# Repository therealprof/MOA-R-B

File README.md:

# The MOA(R)B (or mother of all Rust boards)

The MOA(R)B is a proof of concept proto board which breaks out 4 MCUs from
different vendors which are readily supported by the Rust programming language
and adds a DAP42 USB debugger/programmer with virtual serial port as well as
the requisite USB port and voltage regulator for good measure.

## What exactly is it?

The MOA(R)B was developed to demonstrate how easy it is to design and manufacture Rust-able microcontroller designs. The original plan was to give a talk about this at Oxidize 2019 but that didn't happen. The board is still the first iteration (with a minor fix applied) and I don't expect to further update it. However feel free to take the full or parts of the design and do whatever you want with it.

The following MCUs are supported (but compatible footprints might be used as well):
* ST STM32F042F6Px
* NXP LPC824M201JDH20
* EByte E73-2G4M04S-52832 (a BLE capable module based on the Nordic NRF52832)
* Atmel/Microchip ATSAMD21E15A

In addition another STM32F042F6P6 can be populated as DAPlink compatible debugger/programmer with virtual serial port.

## How to build the boards?

I've included an interactive HTML BOM and population guide [here](bom/ibom.html).

**NOTE**: If you happen to have one of the 10 first run boards you will need to add a shame wire from pad 15 of the DAPlink MCU to ground -- if you want to populate and use the onboard debugger, that is. If you work with the published version 1.1 there're no known errata.

### Functional blocks

* Voltage regulator: If you want to automatic 3.3V generation and distribution, this is a must have. You should also populate J5 then, which connect the 3.3V to the MCUs when the link is shorted
* USB input: You obviously want to have this if you want to power the board from USB and/or use the onboard debugger (in this case you might also want to consider populating the TVS protection diode)
* Debugger: Obviously you only need this if you'd like to have the onboard debugger. The purpose of the SWD connector and J6 is to connect the SWD lines to the onboard debugger but also for standalone conversion if you have an external debugger or you'd like to use this debugger for external devices -- so many choices!
* LEDs: Who doesn't like blinkies? The 4 MCU leds are indicators for powered MCUs the other ones can either be used for the debugger or alternatively for any of the MCUs.
* The MCUs are completely optional and fully broken out to commonly used 2.54mm spacing so populate and use whichever you want to use. The capacitors next to the MCUs should be populated for decoupling. Most likely you also want to have the matching pins on the backside; those can either be long enough straight headers or SMD headers.

## Can I reuse the hardware for my own ideas?

Absolutely, everything is licensed under the BSD license so please go ahead and use it however you'd like.

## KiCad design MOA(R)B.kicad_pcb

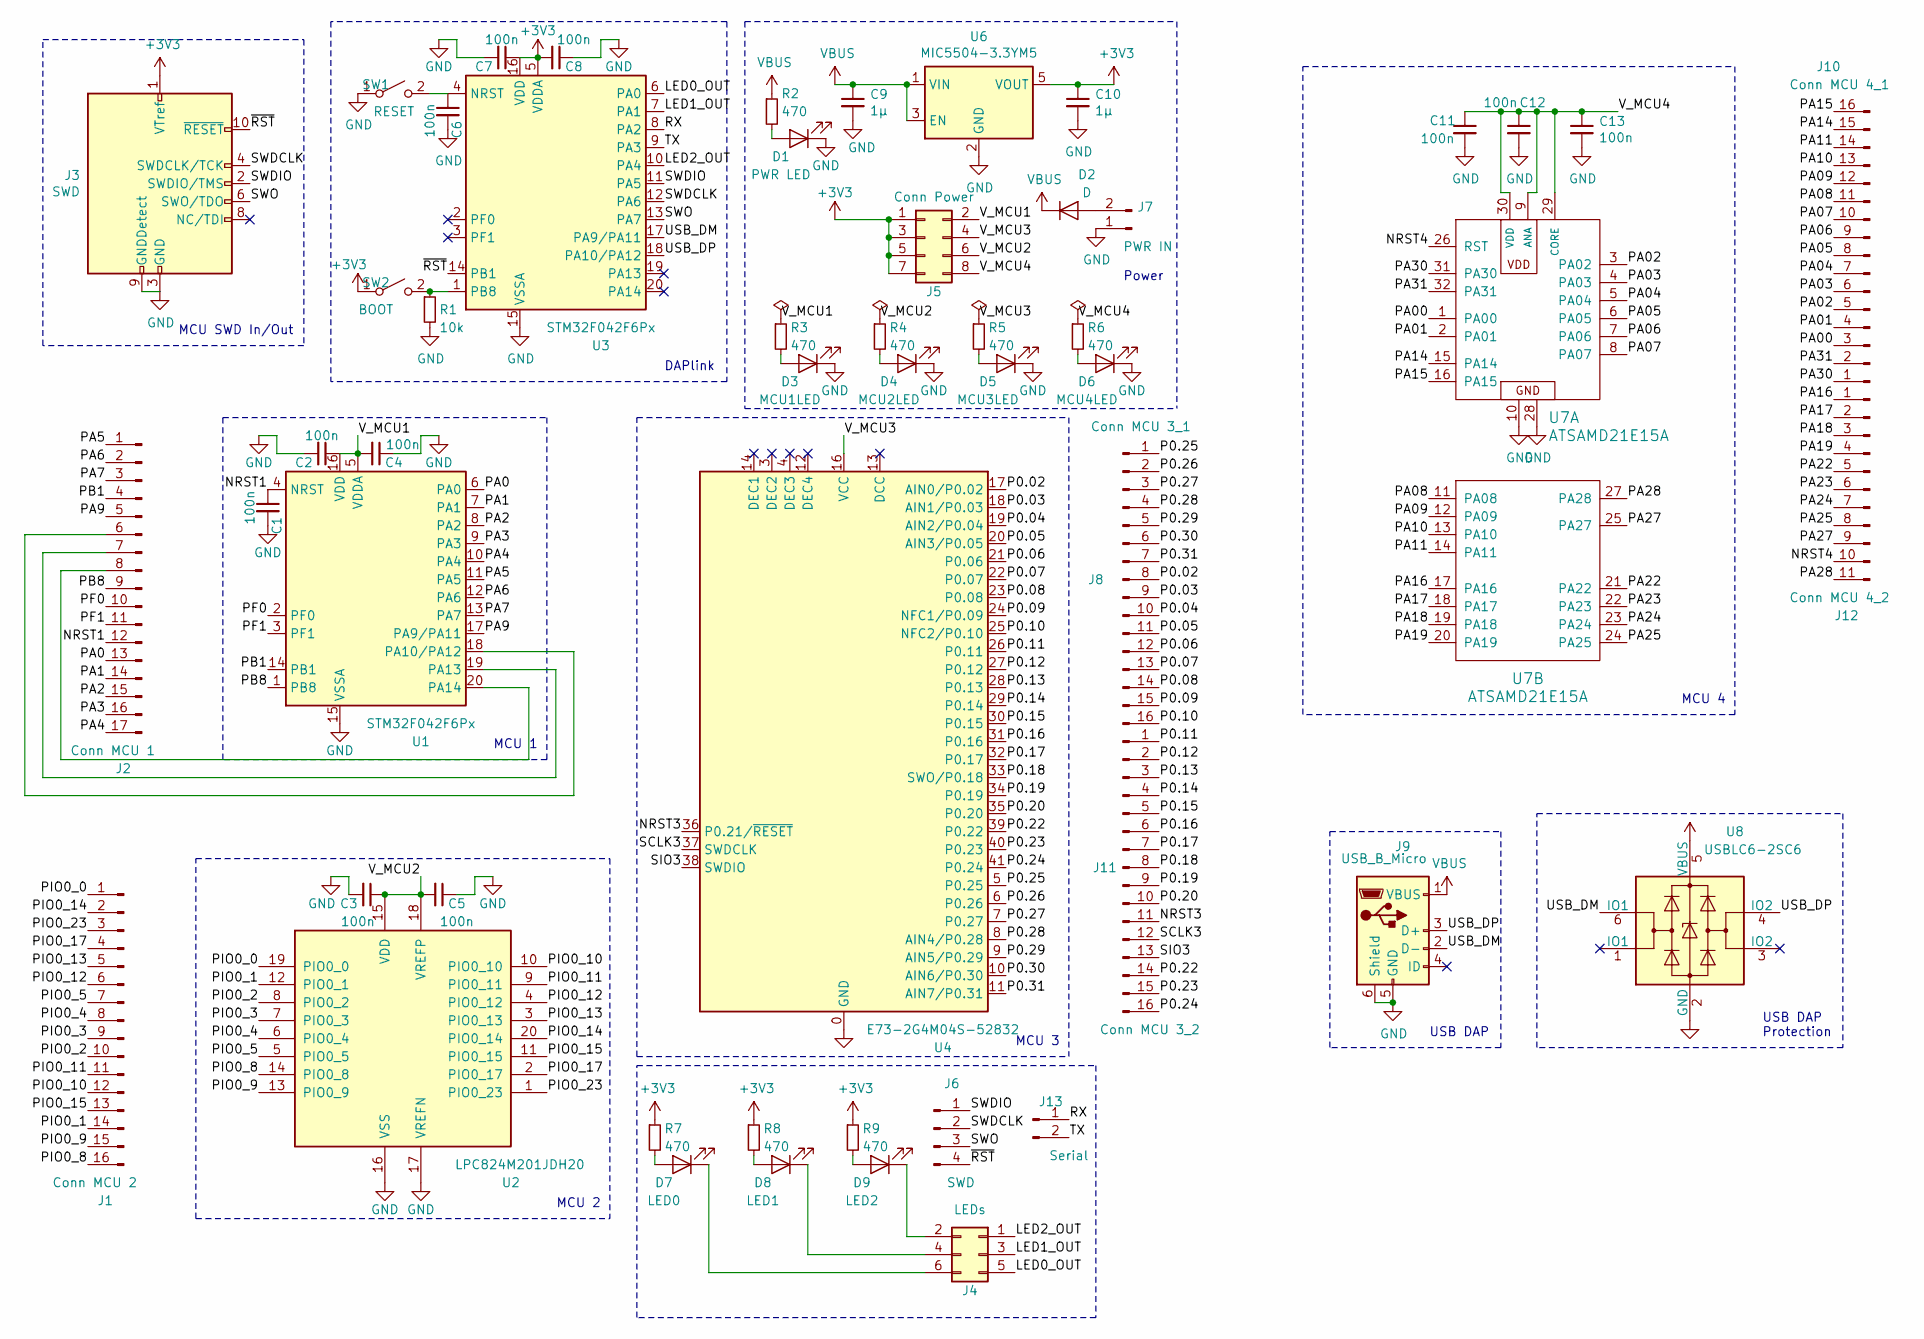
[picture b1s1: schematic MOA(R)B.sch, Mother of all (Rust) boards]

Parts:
C1, C2, C3, C4, C5, C6, C7, C8, C11, C12, C13: 100n; C_0805_2012Metric
C9, C10: 1µ; C_0805_2012Metric
D1: PWR LED; LED_0805_2012Metric
D2: D; D_0805_2012Metric
D3: MCU1LED; LED_0805_2012Metric
D4: MCU2LED; LED_0805_2012Metric
D5: MCU3LED; LED_0805_2012Metric
D6: MCU4LED; LED_0805_2012Metric
D7: LED0; LED_0805_2012Metric
D8: LED1; LED_0805_2012Metric
D9: LED2; LED_0805_2012Metric
J1: Conn MCU 2; Harwin_M20-89016xx_1x16_P2.54mm_Horizontal
J2: Conn MCU 1; Harwin_M20-89017xx_1x17_P2.54mm_Horizontal
J3: SWD; PinHeader_2x05_P1.27mm_Vertical_SMD
J4: LEDs; PinHeader_2x03_P2.54mm_Vertical
J5: Conn Power; PinHeader_2x04_P2.54mm_Vertical
J6: SWD; PinHeader_1x04_P2.54mm_Vertical
J7: PWR IN; PinHeader_1x02_P2.54mm_Vertical
J8: Conn MCU 3_1; Harwin_M20-89016xx_1x16_P2.54mm_Horizontal
J9: USB_B_Micro; USB_Micro-B_Molex-105017-0001
J10: Conn MCU 4_1; Harwin_M20-89016xx_1x16_P2.54mm_Horizontal
J11: Conn MCU 3_2; Harwin_M20-89016xx_1x16_P2.54mm_Horizontal
J12: Conn MCU 4_2; Harwin_M20-89011xx_1x11_P2.54mm_Horizontal
J13: Serial; PinHeader_1x02_P2.54mm_Vertical
R1: 10k; R_0805_2012Metric
R2, R3, R4, R5, R6, R7, R8, R9: 470; R_0805_2012Metric
SW1: RESET; SW_SPST_CK_RS282G05A3
SW2: BOOT; SW_SPST_CK_RS282G05A3
U1, U3: STM32F042F6Px; TSSOP-20_4.4x6.5mm_P0.65mm
U2: LPC824M201JDH20; TSSOP-20_4.4x6.5mm_P0.65mm
U4: E73-2G4M04S-52832; E73-2G4M04S
U6: MIC5504-3.3YM5; SOT-23-5
U7: ATSAMD21E15A; TQFP-32_7x7mm_P0.8mm
U8: USBLC6-2SC6; SOT-23-6

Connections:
+3V3: C7.1, C8.2, C10.1, J3.1 (VTref), J5.1, J5.3, J5.5, J5.7, R7.1, R8.1, R9.1, SW2.1 (A), U3.5 (VDDA), U3.16 (VDD), U6.5 (VOUT)
/LED0_OUT: J4.5, U3.6 (PA0)
/LED1_OUT: J4.3, U3.7 (PA1)
/LED2_OUT: J4.1, U3.10 (PA4)
/NRST1: C1.1, J2.12, U1.4 (NRST)
/NRST3: J11.11, U4.36 (P0.21/~RESET)
/NRST4: J12.10, U7.26 (RST); also elsewhere on the board
/P0.02: J8.8, U4.17 (AIN0/P0.02)
/P0.03: J8.9, U4.18 (AIN1/P0.03)
/P0.04: J8.10, U4.19 (AIN2/P0.04)
/P0.05: J8.11, U4.20 (AIN3/P0.05)
/P0.06: J8.12, U4.21 (P0.06)
/P0.07: J8.13, U4.22 (P0.07)
/P0.08: J8.14, U4.23 (P0.08)
/P0.09: J8.15, U4.24 (NFC1/P0.09)
/P0.10: J8.16, U4.25 (NFC2/P0.10)
/P0.11: J11.1, U4.26 (P0.11)
/P0.12: J11.2, U4.27 (P0.12)
/P0.13: J11.3, U4.28 (P0.13)
/P0.14: J11.4, U4.29 (P0.14)
/P0.15: J11.5, U4.30 (P0.15)
/P0.16: J11.6, U4.31 (P0.16)
/P0.17: J11.7, U4.32 (P0.17)
/P0.18: J11.8, U4.33 (SWO/P0.18)
/P0.19: J11.9, U4.34 (P0.19)
/P0.20: J11.10, U4.35 (P0.20)
/P0.22: J11.14, U4.39 (P0.22)
/P0.23: J11.15, U4.40 (P0.23)
/P0.24: J11.16, U4.41 (P0.24)
/P0.25: J8.1, U4.5 (P0.25)
/P0.26: J8.2, U4.6 (P0.26)
/P0.27: J8.3, U4.7 (P0.27)
/P0.28: J8.4, U4.8 (AIN4/P0.28)
/P0.29: J8.5, U4.9 (AIN5/P0.29)
/P0.30: J8.6, U4.10 (AIN6/P0.30)
/P0.31: J8.7, U4.11 (AIN7/P0.31)
/PA00: J10.3, U7.1 (PA00); also elsewhere on the board
/PA0: J2.13, U1.6 (PA0)
/PA01: J10.4, U7.2 (PA01); also elsewhere on the board
/PA1: J2.14, U1.7 (PA1)
/PA02: J10.5, U7.3 (PA02); also elsewhere on the board
/PA2: J2.15, U1.8 (PA2)
/PA03: J10.6, U7.4 (PA03); also elsewhere on the board
/PA3: J2.16, U1.9 (PA3)
/PA04: J10.7, U7.5 (PA04); also elsewhere on the board
/PA4: J2.17, U1.10 (PA4)
/PA05: J10.8, U7.6 (PA05); also elsewhere on the board
/PA5: J2.1, U1.11 (PA5)
/PA06: J10.9, U7.7 (PA06); also elsewhere on the board
/PA6: J2.2, U1.12 (PA6)
/PA07: J10.10, U7.8 (PA07); also elsewhere on the board
/PA7: J2.3, U1.13 (PA7)
/PA08: J10.11, U7.11 (PA08); also elsewhere on the board
/PA09: J10.12, U7.12 (PA09); also elsewhere on the board
/PA9: J2.5, U1.17 (PA9/PA11)
/PA10: J10.13, U7.13 (PA10); also elsewhere on the board
/PA11: J10.14, U7.14 (PA11); also elsewhere on the board
/PA14: J10.15, U7.15 (PA14); also elsewhere on the board
/PA15: J10.16, U7.16 (PA15); also elsewhere on the board
/PA16: J12.1, U7.17 (PA16); also elsewhere on the board
/PA17: J12.2, U7.18 (PA17); also elsewhere on the board
/PA18: J12.3, U7.19 (PA18); also elsewhere on the board
/PA19: J12.4, U7.20 (PA19); also elsewhere on the board
/PA22: J12.5, U7.21 (PA22); also elsewhere on the board
/PA23: J12.6, U7.22 (PA23); also elsewhere on the board
/PA24: J12.7, U7.23 (PA24); also elsewhere on the board
/PA25: J12.8, U7.24 (PA25); also elsewhere on the board
/PA27: J12.9, U7.25 (PA27); also elsewhere on the board
/PA28: J12.11, U7.27 (PA28); also elsewhere on the board
/PA30: J10.1, U7.31 (PA30); also elsewhere on the board
/PA31: J10.2, U7.32 (PA31); also elsewhere on the board
/PB1: J2.4, U1.14 (PB1)
/PB8: J2.9, U1.1 (PB8)
/PF0: J2.10, U1.2 (PF0)
/PF1: J2.11, U1.3 (PF1)
/PIO0_0: J1.1, U2.19 (PIO0_0)
/PIO0_1: J1.14, U2.12 (PIO0_1)
/PIO0_2: J1.10, U2.8 (PIO0_2)
/PIO0_3: J1.9, U2.7 (PIO0_3)
/PIO0_4: J1.8, U2.6 (PIO0_4)
/PIO0_5: J1.7, U2.5 (PIO0_5)
/PIO0_8: J1.16, U2.14 (PIO0_8)
/PIO0_9: J1.15, U2.13 (PIO0_9)
/PIO0_10: J1.12, U2.10 (PIO0_10)
/PIO0_11: J1.11, U2.9 (PIO0_11)
/PIO0_12: J1.6, U2.4 (PIO0_12)
/PIO0_13: J1.5, U2.3 (PIO0_13)
/PIO0_14: J1.2, U2.20 (PIO0_14)
/PIO0_15: J1.13, U2.11 (PIO0_15)
/PIO0_17: J1.4, U2.2 (PIO0_17)
/PIO0_23: J1.3, U2.1 (PIO0_23)
/RX: J13.1, U3.8 (PA2)
/SCLK3: J11.12, U4.37 (SWDCLK)
/SIO3: J11.13, U4.38 (SWDIO)
/SWDCLK: J3.4 (SWDCLK/TCK), J6.2, U3.12 (PA6)
/SWDIO: J3.2 (SWDIO/TMS), J6.1, U3.11 (PA5)
/SWO: J3.6 (SWO/TDO), J6.3, U3.13 (PA7)
/TX: J13.2, U3.9 (PA3)
/USB_DM: J9.2 (D-), U3.17 (PA9/PA11), U8.6 (IO1)
/USB_DP: J9.3 (D+), U3.18 (PA10/PA12), U8.4 (IO2)
/V_MCU1: C2.1, C4.2, J5.2, R3.1, U1.5 (VDDA), U1.16 (VDD)
/V_MCU2: C3.1, C5.2, J5.6, R4.1, U2.15 (VDD), U2.18 (VREFP)
/V_MCU3: J5.4, R5.1, U4.16 (VCC)
/V_MCU4: C11.1, C12.1, C13.1, J5.8, R6.1, U7.9 (ANA), U7.29 (CORE), U7.30 (VDD); also elsewhere on the board
/~RST: J3.10 (~RESET~), J6.4, U3.14 (PB1)
GND: C1.2, C2.2, C3.2, C4.1, C5.1, C6.2, C7.2, C8.1, C9.2, C10.2, C11.2, C12.2, C13.2, D1.1 (K), D3.1 (K), D4.1 (K), D5.1 (K), D6.1 (K), J3.3 (GND), J3.5 (GND), J3.9 (GNDDetect), J7.1, J9.5 (GND), J9.6 (Shield), R1.2, SW1.1 (A), U1.15 (VSSA), U2.16 (VSS), U2.17 (VREFN), U3.15 (VSSA), U4.0 (GND), U4.1 (GND), U4.2 (GND), U4.15 (GND), U4.42 (GND), U4.43 (GND), U6.2 (GND), U7.10, U7.28, U8.2 (GND); also elsewhere on the board
unnamed: C6.1, SW1.2 (B), U3.4 (NRST)
unnamed: D1.2 (A), R2.2
unnamed: D2.2 (A), J7.2
unnamed: D3.2 (A), R3.2
unnamed: D4.2 (A), R4.2
unnamed: D5.2 (A), R5.2
unnamed: D6.2 (A), R6.2
unnamed: D7.1 (K), J4.6
unnamed: D7.2 (A), R7.2
unnamed: D8.1 (K), J4.4
unnamed: D8.2 (A), R8.2
unnamed: D9.1 (K), J4.2
unnamed: D9.2 (A), R9.2
unnamed: J2.6, U1.18 (PA10/PA12)
unnamed: J2.7, U1.19 (PA13)
unnamed: J2.8, U1.20 (PA14)
unnamed: R1.1, SW2.2 (B), U3.1 (PB8)
VBUS: C9.1, D2.1 (K), J9.1 (VBUS), R2.1, U6.1 (VIN), U6.3 (EN), U8.5 (VBUS)

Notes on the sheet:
DAPlink
MCU 1
MCU 2
MCU 3
MCU 4
Power
USB DAP
USB DAP Protection
MCU SWD In/Out

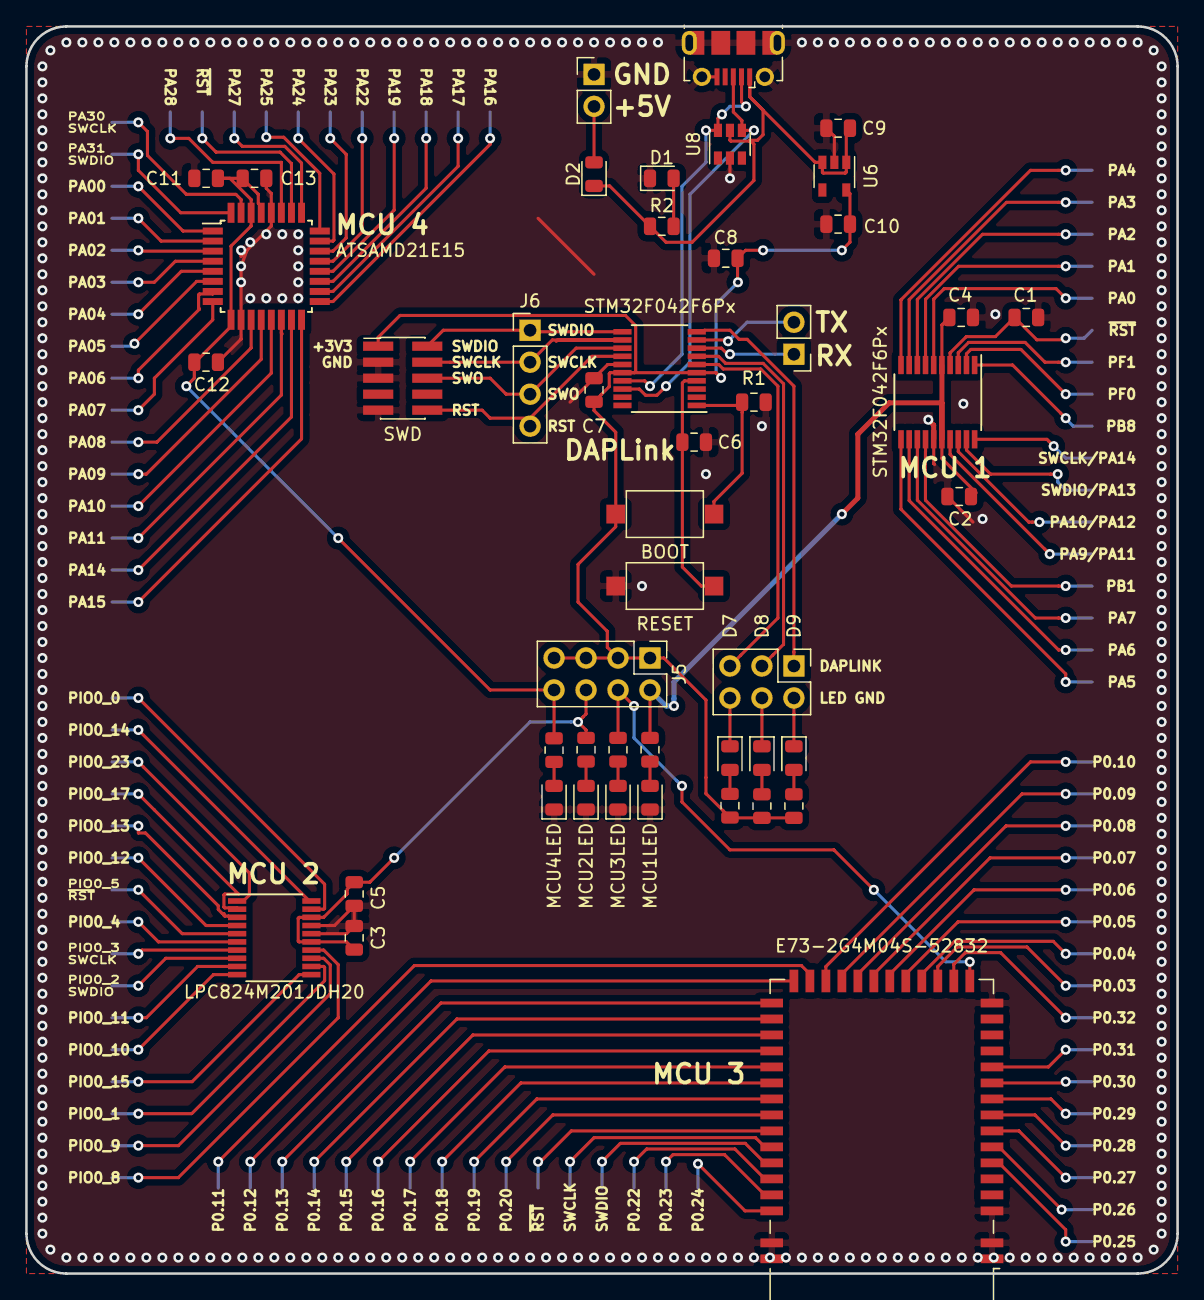
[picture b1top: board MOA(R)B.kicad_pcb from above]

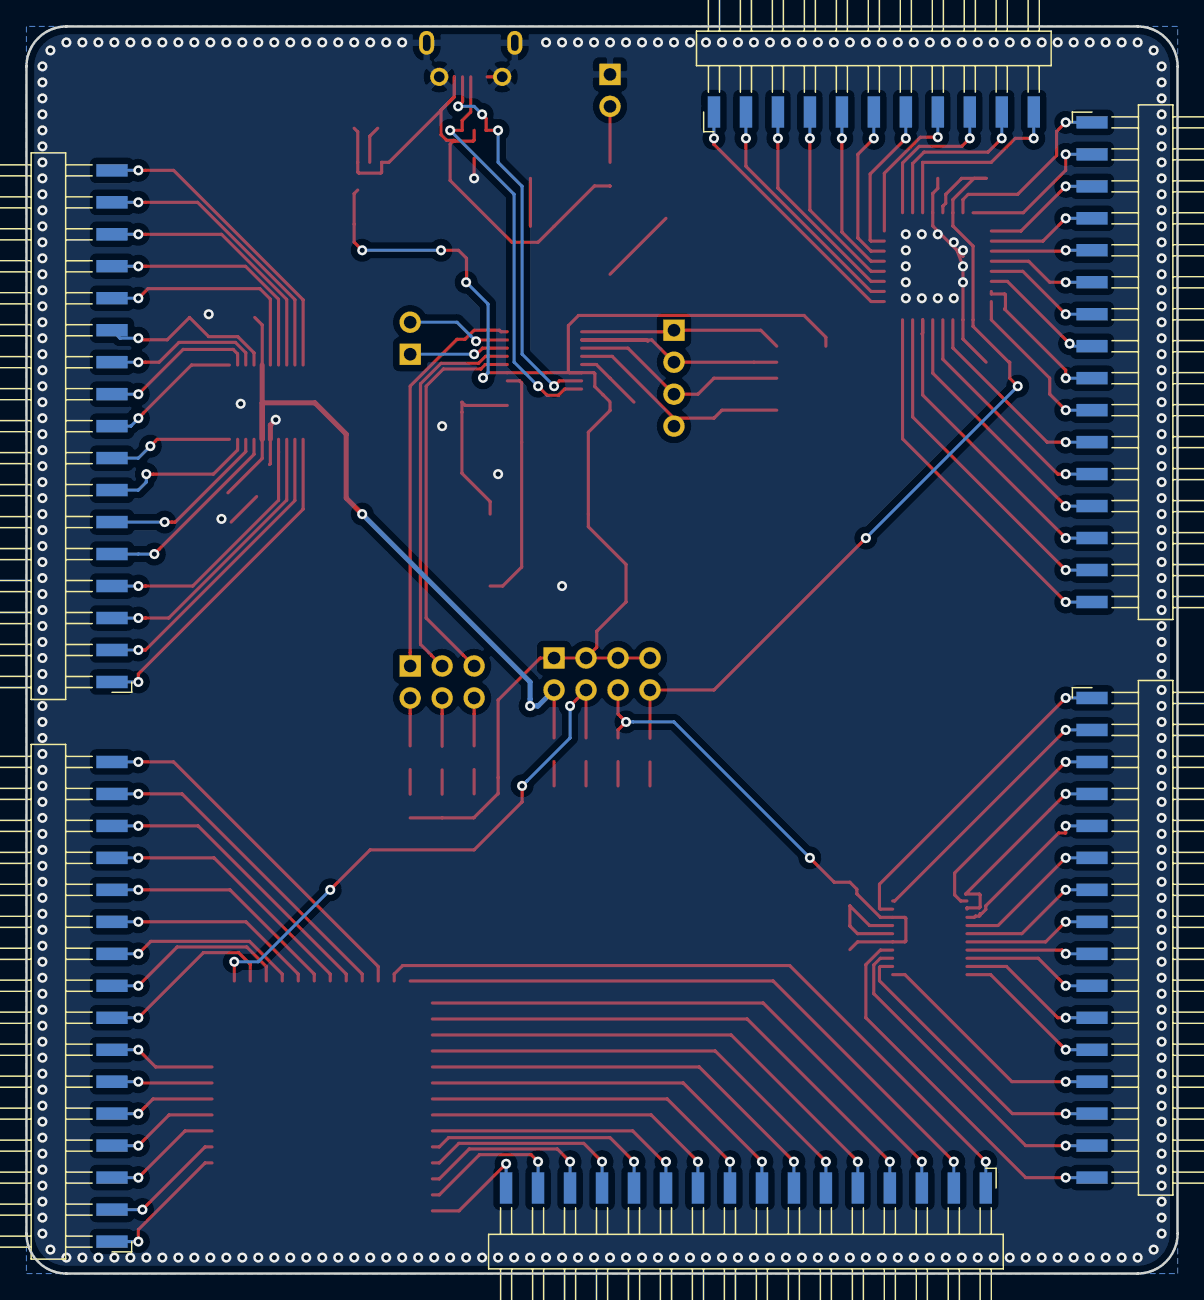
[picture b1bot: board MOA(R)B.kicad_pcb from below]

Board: 2 copper layers, 91.4 x 99.1 mm, 53 parts (6 on the bottom side), 124 nets.

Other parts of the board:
ATSAMD21E15: ATSAMD21E15A; TQFP-32_7x7mm_P0.8mm

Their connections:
/NRST4: ATSAMD21E15.26; also elsewhere on the board
/PA00: ATSAMD21E15.1; also elsewhere on the board
/PA01: ATSAMD21E15.2; also elsewhere on the board
/PA02: ATSAMD21E15.3; also elsewhere on the board
/PA03: ATSAMD21E15.4; also elsewhere on the board
/PA04: ATSAMD21E15.5; also elsewhere on the board
/PA05: ATSAMD21E15.6; also elsewhere on the board
/PA06: ATSAMD21E15.7; also elsewhere on the board
/PA07: ATSAMD21E15.8; also elsewhere on the board
/PA08: ATSAMD21E15.11; also elsewhere on the board
/PA09: ATSAMD21E15.12; also elsewhere on the board
/PA10: ATSAMD21E15.13; also elsewhere on the board
/PA11: ATSAMD21E15.14; also elsewhere on the board
/PA14: ATSAMD21E15.15; also elsewhere on the board
/PA15: ATSAMD21E15.16; also elsewhere on the board
/PA16: ATSAMD21E15.17; also elsewhere on the board
/PA17: ATSAMD21E15.18; also elsewhere on the board
/PA18: ATSAMD21E15.19; also elsewhere on the board
/PA19: ATSAMD21E15.20; also elsewhere on the board
/PA22: ATSAMD21E15.21; also elsewhere on the board
/PA23: ATSAMD21E15.22; also elsewhere on the board
/PA24: ATSAMD21E15.23; also elsewhere on the board
/PA25: ATSAMD21E15.24; also elsewhere on the board
/PA27: ATSAMD21E15.25; also elsewhere on the board
/PA28: ATSAMD21E15.27; also elsewhere on the board
/PA30: ATSAMD21E15.31; also elsewhere on the board
/PA31: ATSAMD21E15.32; also elsewhere on the board
/V_MCU4: ATSAMD21E15.9, ATSAMD21E15.29, ATSAMD21E15.30; also elsewhere on the board
GND: ATSAMD21E15.10, ATSAMD21E15.28; also elsewhere on the board

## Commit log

2019-04-28 First revision
2019-04-28 Fixed typos in README.md
2019-04-28 Another typo fix
